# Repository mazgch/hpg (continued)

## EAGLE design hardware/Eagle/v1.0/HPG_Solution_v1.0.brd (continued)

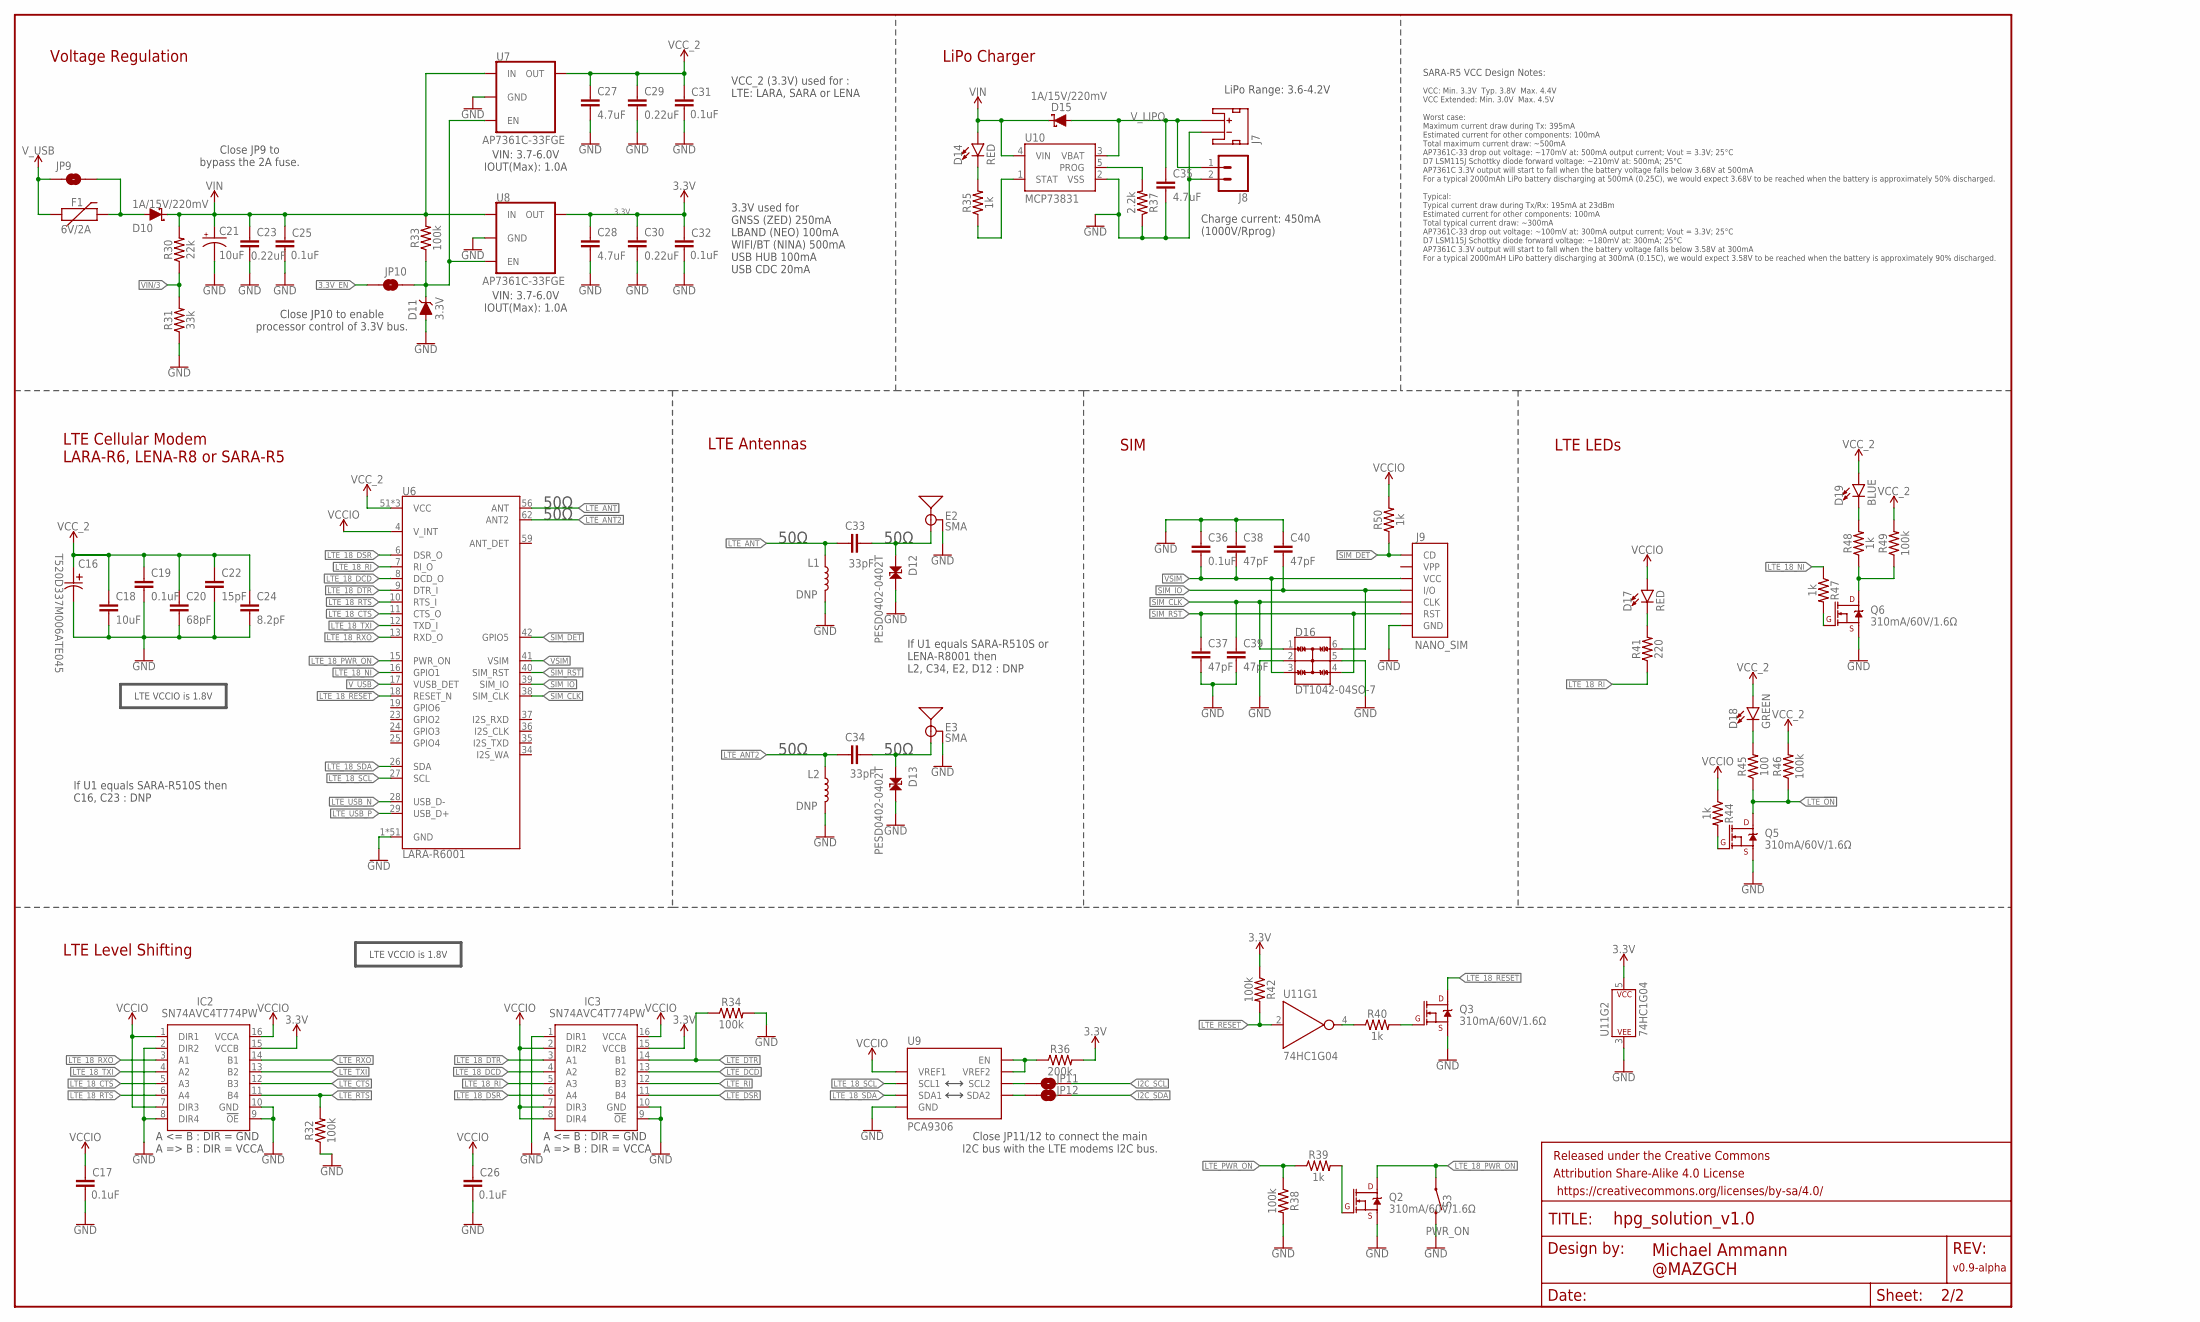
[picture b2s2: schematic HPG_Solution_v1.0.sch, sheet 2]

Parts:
C16: T520D337M006ATE045; CAPMP7.6X4.3_3.1N_KEM
C17, C19, C25, C26, C31, C32, C36: 0.1uF; 0603
C18: 10uF; 0603
C20: 68pF; 0603@1
C21: 10uF; EIA3216
C22: 15pF; 0603
C23, C29, C30: 0.22uF; 0603
C24: 8.2pF; 0603
C27, C28, C35: 4.7uF; 0603
C33, C34: 33pF; 0402
C37, C38, C39, C40: 47pF; 0603
D10, D15: 1A/15V/220mV; DO-214BA
D11: 3.3V; SOD-323
D12, D13: PESD0402-0402T; 0402-TIGHT
D14, D17: RED; LED-0603
D16: DT1042-04SO-7; SOT23-6L
D18: GREEN; LED-0603
D19: BLUE; LED-0603
E2, E3: SMA; SMA-EDGE
F1: 6V/2A; 1210
FRAME3: FRAME-LEDGER; CREATIVE_COMMONS
IC2, IC3: SN74AVC4T774PW; SOP65P640X120-16N
J7: JST_2MM_MALE; JST-2-SMD
J8: CONN_021X02_NO_SILK; 1X02_NO_SILK
J9: NANO_SIM; NANO_SIM_PP
JP9, JP10, JP11, JP12: JUMPER-SMT_2_NO_SILK; SMT-JUMPER_2_NO_SILK
L1, L2: DNP; 0402_COILCRAFT
Q2, Q3, Q5, Q6: 310mA/60V/1.6Ω; SOT323
R30: 22k; 0603
R31: 33k; 0603
R32, R33, R34, R38, R42, R46, R49: 100k; 0603
R35, R39, R40, R44, R47, R48, R50: 1k; 0603
R36: 200k; 0603
R37: 2.2k; 0603
R41: 220; 0603
R45: 100; 0603
S3: PWR_ON; TACTILE_SWITCH_SMD_5.2MM
U6: LARA-R6001; LARA-LGA
U7, U8: AP7361C-33FGE; UDFN-8
U9: PCA9306; VSSOP_8PIN
U10: MCP73831; SOT23-5
U11: 74HC1G04; SOT353

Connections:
3.3V: C28.1, C30.1, C32.1, IC2.15 (VCCB), IC3.15 (VCCB), R36.2, R42.1, U8.1 (OUT), U11.5 (P$V+); also elsewhere on the board
3.3V_EN: JP10.1; also elsewhere on the board
CHG_LED: R35.1, U10.1 (STAT)
GND: C16.2, C17.2, C18.2, C19.2, C20.2, C21.-, C22.2, C23.2, C24.2, C25.2, C26.2, C27.2, C28.2, C29.2, C30.2, C31.2, C32.2, C35.2, C36.1, C37.2, C38.1, C39.2, C40.1, D11.A, D12.2, D13.2, D16.2, D16.5, E2.GND@0 (GND), E2.GND@1 (GND), E2.GND@2 (GND), E2.GND@3 (GND), E3.GND@0 (GND), E3.GND@1 (GND), E3.GND@2 (GND), E3.GND@3 (GND), IC2.2 (DIR2), IC2.8 (DIR4), IC2.9 (!OE), IC2.10 (GND), IC3.1 (DIR1), IC3.9 (!OE), IC3.10 (GND), J7.1 (-), J8.2, J9.A1 (GND), J9.A2 (GND), J9.A3 (GND), J9.A4 (GND), J9.C5 (GND), L1.P$2 (2), L2.P$2 (2), Q2.2 (S), Q3.2 (S), Q5.2 (S), Q6.2 (S), R31.1, R32.1, R34.2, R37.1, R38.2, S3.3 (2), S3.4 (2), U6.1 (GND), U6.3 (GND), U6.5 (GND), U6.14 (GND), U6.20 (GND), U6.21 (GND), U6.22 (GND), U6.30 (GND), U6.32 (GND), U6.43 (GND), U6.50 (GND), U6.54 (GND), U6.55 (GND), U6.57 (GND), U6.58 (GND), U6.60 (GND), U6.61 (GND), U6.63 (GND), U6.64 (GND), U6.65 (GND), U6.66 (GND), U6.67 (GND), U6.68 (GND), U6.69 (GND), U6.70 (GND), U6.71 (GND), U6.72 (GND), U6.73 (GND), U6.74 (GND), U6.75 (GND), U6.76 (GND), U6.77 (GND), U6.78 (GND), U6.79 (GND), U6.80 (GND), U6.81 (GND), U6.82 (GND), U6.83 (GND), U6.84 (GND), U6.85 (GND), U6.86 (GND), U6.87 (GND), U6.88 (GND), U6.89 (GND), U6.90 (GND), U6.91 (GND), U6.92 (GND), U6.93 (GND), U6.94 (GND), U6.95 (GND), U6.96 (GND), U7.4 (GND), U7.EP (GND), U8.4 (GND), U8.EP (GND), U9.P1 (GND), U10.2 (VSS), U11.3 (P$V-); also elsewhere on the board
I2C_SCL: JP11.2; also elsewhere on the board
I2C_SDA: JP12.2; also elsewhere on the board
LTE_18_!RESET!: Q3.3 (D), U6.18 (RESET_N)
LTE_18_CTS: IC2.5 (A3), U6.11 (CTS_O)
LTE_18_DCD: IC3.4 (A2), U6.8 (DCD_O)
LTE_18_DSR: IC3.6 (A4), U6.6 (DSR_O)
LTE_18_DTR: IC3.3 (A1), U6.9 (DTR_I)
LTE_18_NI: R47.1, U6.16 (GPIO1)
LTE_18_PWR_ON: Q2.3 (D), S3.1, S3.2 (1), U6.15 (PWR_ON)
LTE_18_RI: IC3.5 (A3), R41.1, U6.7 (RI_O)
LTE_18_RTS: IC2.6 (A4), U6.10 (RTS_I)
LTE_18_RXO: IC2.3 (A1), U6.13 (RXD_O)
LTE_18_SCL: U6.27 (SCL), U9.P3 (SCL1)
LTE_18_SDA: U6.26 (SDA), U9.P4 (SDA1)
LTE_18_TXI: IC2.4 (A2), U6.12 (TXD_I)
LTE_!ON!: Q5.3 (D), R45.1, R46.1; also elsewhere on the board
LTE_!RESET!: R42.2, U11.2 (A); also elsewhere on the board
LTE_ANT: C33.1, L1.P$1 (1), U6.56 (ANT)
LTE_ANT2: C34.1, L2.P$1 (1), U6.62 (ANT2)
LTE_CTS: IC2.12 (B3); also elsewhere on the board
LTE_DCD: IC3.13 (B2); also elsewhere on the board
LTE_DSR: IC3.11 (B4); also elsewhere on the board
LTE_DTR: IC3.14 (B1), R34.1; also elsewhere on the board
LTE_PWR_ON: R38.1, R39.1; also elsewhere on the board
LTE_RI: IC3.12 (B3); also elsewhere on the board
LTE_RTS: IC2.11 (B4), R32.2; also elsewhere on the board
LTE_RXO: IC2.14 (B1); also elsewhere on the board
LTE_SCL: JP11.1, U9.P6 (SCL2)
LTE_SDA: JP12.1, U9.P5 (SDA2)
LTE_TXI: IC2.13 (B2); also elsewhere on the board
LTE_USB_N: U6.28 (USB_D-); also elsewhere on the board
LTE_USB_P: U6.29 (USB_D+); also elsewhere on the board
unnamed: C34.2, D13.1, E3.SIG (SIGNAL)
unnamed: D10.A, F1.2, JP9.2
unnamed: C33.2, D12.1, E2.SIG (SIGNAL)
unnamed: R37.2, U10.5 (PROG)
unnamed: D14.C, R35.2
unnamed: R36.1, U9.P7 (VREF2), U9.P8 (EN)
unnamed: Q2.1 (G), R39.2
unnamed: Q3.1 (G), R40.2
unnamed: R40.1, U11.4 (Y)
unnamed: D17.C, R41.2
unnamed: Q6.1 (G), R47.2
unnamed: Q6.3 (D), R48.1, R49.1
unnamed: D19.C, R48.2
unnamed: Q5.1 (G), R44.2
unnamed: D18.C, R45.2
unnamed: D11.C, JP10.2, R33.1, U7.5 (EN), U8.5 (EN)
SIM_CLK: C39.1, D16.1, J9.C3 (CLK), U6.38 (SIM_CLK)
SIM_DET: J9.CD, R50.1, U6.42 (GPIO5)
SIM_IO: C40.2, D16.6, J9.C7 (I/O), U6.39 (SIM_IO)
SIM_RST: C37.1, D16.4, J9.C2 (RST), U6.40 (SIM_RST)
VCCIO: C17.1, C26.1, D17.A, IC2.1 (DIR1), IC2.7 (DIR3), IC2.16 (VCCA), IC3.2 (DIR2), IC3.7 (DIR3), IC3.8 (DIR4), IC3.16 (VCCA), R44.1, R50.2, U6.4 (V_INT), U9.P2 (VREF1)
VCC_2: C16.1, C18.1, C19.1, C20.1, C22.1, C24.1, C27.1, C29.1, C31.1, D18.A, D19.A, R46.2, R49.2, U6.51 (VCC), U6.52 (VCC), U6.53 (VCC), U7.1 (OUT)
VIN: C21.+, C23.1, C25.1, D10.C, D14.A, D15.C, R30.2, R33.2, U7.8 (IN), U8.8 (IN), U10.4 (VIN); also elsewhere on the board
VIN/3: R30.1, R31.2; also elsewhere on the board
VSIM: C36.2, C38.2, D16.3, J9.C1 (VCC), U6.41 (VSIM)
V_LIPO: C35.1, D15.A, J7.2 (+), J8.1, U10.3 (VBAT)
V_USB: F1.1, JP9.1, U6.17 (VUSB_DET); also elsewhere on the board

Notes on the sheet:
SARA-R5 VCC Design Notes:
VCC: Min. 3.3V Typ. 3.8V Max. 4.4V VCC Extended: Min. 3.0V Max. 4.5V Worst case: Maximum current draw during Tx: 395mA Estimated current for other components: 100mA Total maximum current draw: ~500mA AP7361C-33 drop out voltage: ~170mV at: 500mA output current; Vout = 3.3V; 25°C D7 LSM115J Schottky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
Michael Ammann @MAZGCH
Voltage Regulation
VIN: 3.7-6.0V IOUT(Max): 1.0A
Close JP10 to enable processor control of 3.3V bus.
LiPo Charger
LiPo Range: 3.6-4.2V
Charge current: 450mA (1000V/Rprog)
VCC_2 (3.3V) used for : LTE: LARA, SARA or LENA
3.3V used for GNSS (ZED) 250mA LBAND (NEO) 100mA WIFI/BT (NINA) 500mA USB HUB 100mA USB CDC 20mA
Close JP9 to bypass the 2A fuse.
LTE Cellular Modem LARA-R6, LENA-R8 or SARA-R5
SIM
50Ω
LTE VCCIO is 1.8V
If U1 equals SARA-R510S then C16, C23 : DNP
LTE Antennas
If U1 equals SARA-R510S or LENA-R8001 then L2, C34, E2, D12 : DNP
LTE LEDs
LTE Level Shifting
Close JP11/12 to connect the main I2C bus with the LTE modems I2C bus.
v0.9-alpha

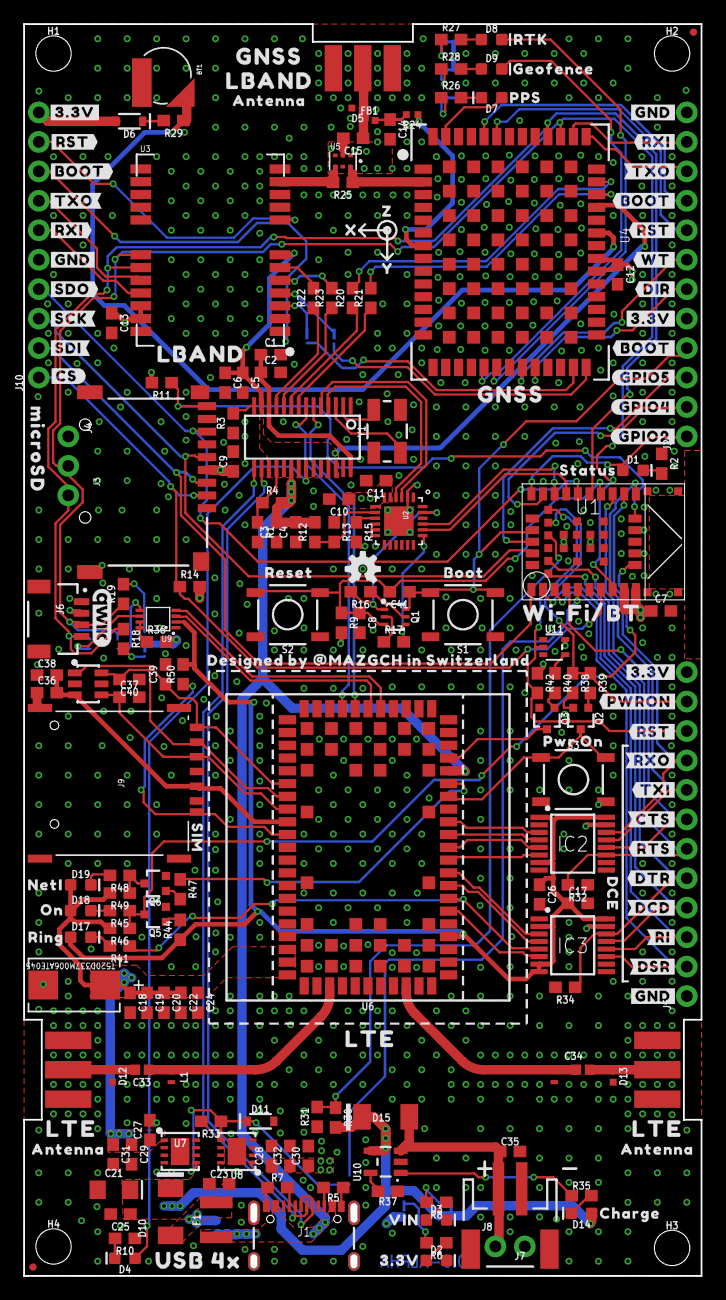
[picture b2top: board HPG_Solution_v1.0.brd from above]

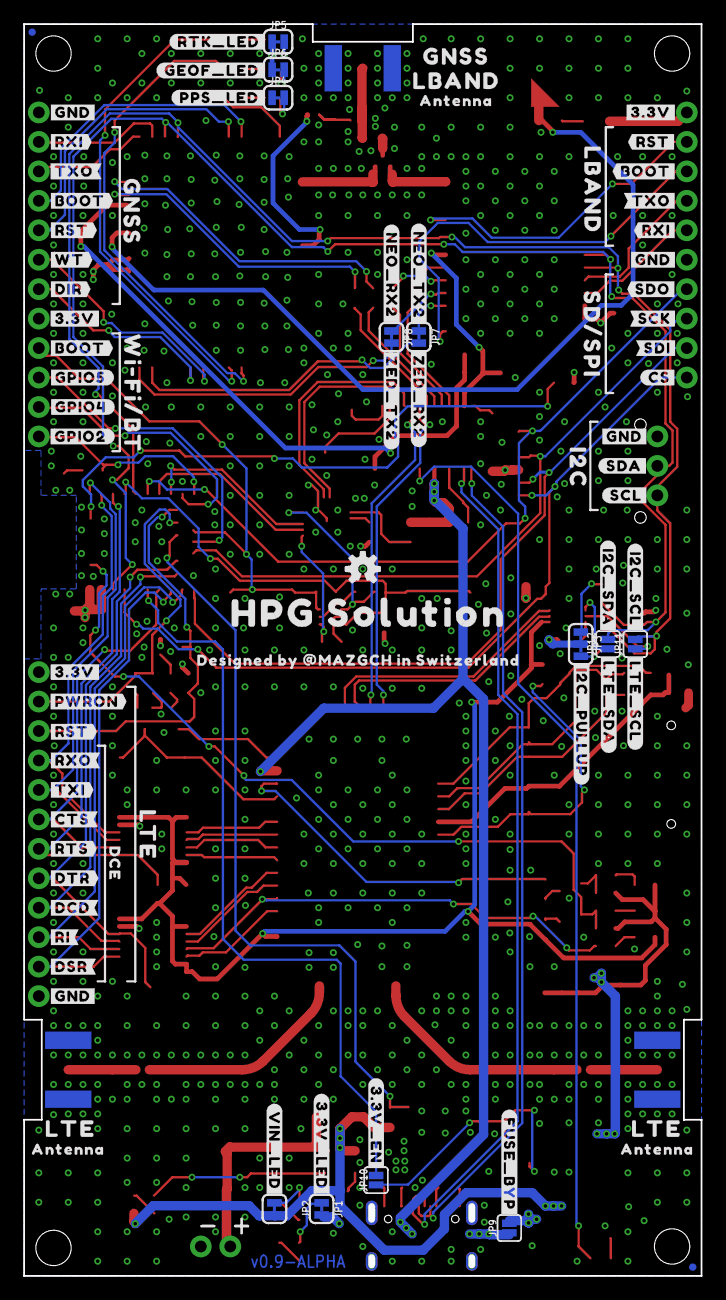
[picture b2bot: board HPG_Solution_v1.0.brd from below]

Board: 4 copper layers, 58.4 x 108.0 mm, 311 parts (84 on the bottom side), 141 nets.

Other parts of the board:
U$1, U$122: OSHW-LOGO-S
U$2: QWIIC_5MM
U$3: MICROSD0
U$4, U$5, U$19, U$44, U$45, U$118: LTE0
U$6, U$20, U$46, U$116: GNSS0
U$7: #PWRON#1
U$8, U$9, U$10, U$37, U$40, U$43, U$138: #GND#0
U$11, U$12, U$13, U$36, U$39, U$41: #3#3V#0
U$14, U$126, U$127: #RST#2
U$15: RESET6
U$16: BOOT5
U$17: PWR_ON0
U$18, U$22, U$35: #RST#3
U$21: CHARGE0
U$23: #RTK_LED#0
U$24: #3#3V_LED#0
U$25: 3#3V3
U$26: RTK16
U$27: #I2C_SCL#2
U$28: PPS14
U$29: #I2C_PULLUP#3
U$30, U$59: #RXI#1
U$31: ON0
U$32, U$33: #TXO#5
U$34: #CS#4
U$38, U$60: #RXI#0
U$42: #GEOF_LED#1
U$47: X1
U$48: Y2
U$49: #I2C_SDA#1
U$50: HPG_SOLUTION0
U$51: SIM0
U$52: Z0
U$53, U$75, U$76: #BOOT#1
U$54: VIN3
U$55: I2C0
U$56: #PWRON#0
U$57, U$72, U$74: #BOOT#0
U$58, U$61: #TXO#3
U$62: #PPS_LED#2
U$63: #GPIO4#1
U$64: #GPIO2#2
U$65: #GPIO2#8
U$66: #DIR#13
U$67: #WT#11
U$68: #WT#10
U$69: #DIR#12
U$70: #GPIO4#7
U$71: #GPIO5#6
U$73, U$114: DCE0
U$77, U$78, U$82, U$117: LBAND2
U$79: USB_4X3
U$80: RING0
U$81: STATUS7
U$83: #LTE_SCL#7
U$84, U$85, U$86, U$87, U$88, U$89: ANTENNA2
U$90, U$119: WI#FI#BT3
U$91: #3#3V_EN#1
U$92: #CTS#5
U$93: #DCD#4
U$94: #FUSE_BYP#2
U$95: #DSR#3
U$96: #DTR#7
U$97: #RI#6
U$98: #RXO#2
U$99: #RTS#8
U$100: #TXI#1
U$101: #RXO#3
U$102: #TXI#2
U$103: #CTS#6
U$104: #RTS#9
U$105: #DTR#8
U$106: #DCD#5
U$107: #RI#7
U$108: #DSR#4
U$109: #SCK#0
U$110: #NEO_RX2#0
U$111: #NEO_TX2#2
U$112: #ZED_RX2#3
U$113: #ZED_TX2#1
U$115: #GPIO5#0
U$120, U$121: DESIGNED_BY_#MAZGCH_IN_SWITZERLAND3
U$123: #LTE_SDA#5
U$124: #SCK#4
U$125: GEOFENCE5
U$128: #SDI#1
U$129: #VIN_LED#4
U$130: #SDO#2
U$131: #CS#3
U$132: #SDI#5
U$133: #SDO#6
U$134: SD#SPI8
U$135: NETI9
U$136: #SCL#11
U$137: #SDA#12

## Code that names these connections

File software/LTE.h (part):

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  /** constructor
   *  \note we do not pass the pins to the class as we prefer to be in control of them 
   */
  LTE() : SARA_R5{ PIN_INVALID/*LTE_PWR_ON*/, PIN_INVALID/*LTE_RESET*/, 3/*retries*/ } { 
    state = INIT;
    restart = false;
    ntripSocket = -1;
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      setState(CHECKSIM);  
    }
    while(true) {
      if ((PIN_INVALID != LTE_ON) && (state != INIT)) {
        // detect if LTE was turned off
        if (LTE_ON_ACTIVE != digitalRead(LTE_ON)) {
          UbxSerial.end();
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   *  The pins are defined in the HW.h file and depend on the board compiled for. 
   */
  void hwInit(void) {
    // The current SARA-R5 library is setting the LTE_RESET and LTE_PWR_ON pins to input after using them, 
    // This is not ideal for the v0.8/v0.9 hardware. Therefore it is prefered to control the LTE_RESET 
    // and LTE_PWR_ON externally in our code here. We also like to have better control of the pins to 
    // support different variants of LTE modems.
         
    // Module     Power On time   Power Off time   Reset
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    // LARA-R6    0.15-3.2s       >1.5s            0.05-6s (10s emergency)
    // LENA-R8    >2s             >3.1s            0.05s
    
    // The LTE_RESET pin is active LOW, HIGH = idle, LOW = in reset
    // The LTE_RESET pin unfortunately does not have a pull up resistor on the v0.8/v0.9 hardware
    if (PIN_INVALID != LTE_RESET) {
      HW::pinModeWrite(LTE_RESET, HIGH);
    }
    // The LTE_PWR_ON pin is usually active HIGH, LOW = idle, defined by LTE_PWR_ON_ACTIVE, active timings see table above
    // The LTE_PWR_ON pin has a external pull low resistor on the board. 
    if (PIN_INVALID != LTE_PWR_ON) {
      HW::pinModeWrite(LTE_PWR_ON, !LTE_PWR_ON_ACTIVE);
    }
    if (PIN_INVALID != LTE_TXI) {
      HW::pinModeWrite(LTE_TXI, HIGH);
    }
    if (PIN_INVALID != LTE_RTS) {
      HW::pinModeWrite(LTE_RTS, LOW);
    }
    if (PIN_INVALID != LTE_DTR) {
      HW::pinModeWrite(LTE_DTR, LOW);
    } 
    // init all other pins here
    if (PIN_INVALID != LTE_ON)  pinMode(LTE_ON,  INPUT);
    if (PIN_INVALID != LTE_RXO) pinMode(LTE_RXO, INPUT);
    if (PIN_INVALID != LTE_CTS) pinMode(LTE_CTS, INPUT);
    if (PIN_INVALID != LTE_DSR) pinMode(LTE_DSR, INPUT);
    if (PIN_INVALID != LTE_DCD) pinMode(LTE_DCD, INPUT); 
    if (PIN_INVALID != LTE_RI)  pinMode(LTE_RI,  INPUT);
    if (PIN_INVALID != LTE_INT) pinMode(LTE_INT, INPUT);
  }

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    // turn on the module 
    #define DETECT_DELAY 100
    int pwrOnTime = -1; // will never trigger
    if (PIN_INVALID != LTE_PWR_ON) {
      if ((PIN_INVALID != LTE_ON) ? LTE_ON_ACTIVE != digitalRead(LTE_ON) : true) {
        log_i("LTE power on");
        digitalWrite(LTE_PWR_ON, LTE_PWR_ON_ACTIVE);
        pwrOnTime = LTE_POWER_ON_PULSE / DETECT_DELAY;
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        pwrOnTime = -1; // no more
        i = 0; // restart timer
      }
      if (PIN_INVALID != LTE_RXO) {
        char rxo = digitalRead(LTE_RXO);
        if (lastRxo != rxo) {
          log_d("LTE pin RXO %s", (rxo == LOW) ? "LOW(active)" : "HIGH(idle)"); 
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        }
        ready = ready && (rxo == HIGH);
      }
      if (PIN_INVALID != LTE_ON) {
        char on = digitalRead(LTE_ON);
        if (on != lastOn) {
          log_d("LTE pin ON %s", (on == LTE_ON_ACTIVE) ? "on(active)" : "off(idle)"); 
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        }
        ready = ready && (on == LTE_ON_ACTIVE);
      }
      if (PIN_INVALID != LTE_CTS) {
        char cts = digitalRead(LTE_CTS);
        if (lastCts != cts) {
          log_d("LTE pin CTS %s", (cts == LOW) ? "LOW(idle)" : "HIGH(wait)"); 
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    if (ready) {
      #define PIN_TXT(pin) (PIN_INVALID == pin) ? "" : digitalRead(pin) == LOW ? " LOW" : " HIGH"
      log_d("baudrate %d pins RXo %d%s TXi %d%s CTSo %d%s RTSi %d%s", LTE_BAUDRATE, 
        LTE_RXO, PIN_TXT(LTE_RXO), LTE_TXI, PIN_TXT(LTE_TXI),
        LTE_CTS, PIN_TXT(LTE_CTS), LTE_RTS, PIN_TXT(LTE_RTS));
      ready = begin(UbxSerial, LTE_BAUDRATE);
    }
    return ready;
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    delay(100);
    UbxSerial.end();
    delay(10);
    log_d("LTE baudrate %d pins RXo %d TXi %d CTSo %d RTSi %d", baud, LTE_RXO, LTE_TXI, LTE_CTS, LTE_RTS);
    UbxSerial.begin(baud, SERIAL_8N1, LTE_RXO, LTE_TXI);
    if ((PIN_INVALID != LTE_RTS) && (PIN_INVALID != LTE_CTS)) {
      UbxSerial.setPins(LTE_RXO, LTE_TXI, LTE_CTS, LTE_RTS); 
      UbxSerial.setHwFlowCtrlMode(HW_FLOWCTRL_CTS_RTS, 64);
    }
    delay(100);
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
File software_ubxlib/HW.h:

/*
 * Copyright 2022 by Michael Ammann (@mazgch)
 *
 * Licensed under the Apache License, Version 2.0 (the "License");
 * you may not use this file except in compliance with the License.
 * You may obtain a copy of the License at
 *
    http://www.apache.org/licenses/LICENSE-2.0
 *
 * Unless required by applicable law or agreed to in writing, software
 * distributed under the License is distributed on an "AS IS" BASIS,
 * WITHOUT WARRANTIES OR CONDITIONS OF ANY KIND, either express or implied.
 * See the License for the specific language governing permissions and
 * limitations under the License.
 */
 
#ifndef __HW_H__
#define __HW_H__

#if defined(ARDUINO_UBLOX_NINA_W10)
 #define HW_TARGET     MAZGCH_HPG_SOLUTION_V09
#elif defined(ARDUINO_UBLOX_NORA_W10)
 #define HW_TARGET     MAZGCH_HPG_MODULAR_V01
#elif defined(ARDUINO_ESP32_MICROMOD)
 #define HW_TARGET     SPARKFUN_MICROMOD_MAINBOARD
#else
 #error unknown board target 
#endif

#define MAZGCH_HPG_SOLUTION_V08              0 // Select ESP32 Arduino / u-blox NINA-W10 series (ESP32) 
#define MAZGCH_HPG_SOLUTION_V09              1 // Select ESP32 Arduino / u-blox NINA-W10 series (ESP32) 
#define MAZGCH_HPG_SOLUTION_V10              2 // Select ESP32 Arduino / u-blox NINA-W10 series (ESP32) 

#define MAZGCH_HPG_MODULAR_V01               5 // Select ESP32 Arduino / u-blox NORA-W10 series (ESP32-S3), LTE in slot 1

#define SPARKFUN_MICROMOD_MAINBOARD_PT      11 // Choose Spakfun ESP32 Arduino / Sparkfun ESP32 MicroMod / prototype LTE function
#define SPARKFUN_MICROMOD_MAINBOARD         12

#define SPARKFUN_MICROMOD_MAINBOARD_DOUBLE  21 // Choose Spakfun ESP32 Arduino / Sparkfun ESP32 MicroMod 

#define SPARKFUN_MICROMOD_ASSET_TRACKER     10 // Choose Spakfun ESP32 Arduino / Sparkfun ESP32 MicroMod

enum HW_PINS {  
    // Standard pins
    BOOT         = 0, 
#if (HW_TARGET == MAZGCH_HPG_MODULAR_V01)
    LED         =  8,
    CDC_RX      = 44,  CDC_TX         = 43,
    CAN_RX      = -1,  CAN_TX         = -1,
    I2C_SDA     = 18,  I2C_SCL        = 17,
#else
    LED         =  2,
    CDC_RX      =  3,  CDC_TX         = 1,
    CAN_RX      =  4,  CAN_TX         = 5,
    I2C_SDA     = 21,  I2C_SCL        = 22,
#endif    
#if (HW_TARGET == MAZGCH_HPG_SOLUTION_V08)
    // LTE (DCE) - BUG 34/39 are input only.on V0.8 -> will swap in V0.9
    LTE_RESET   = -1 /*BUG 34 is IN only */, 
    LTE_PWR_ON  = -1 /*BUG 39 is IN only */,  LTE_ON        = 37,  LTE_INT = -1,
    LTE_TXI     = 25,   LTE_RXO        = 26,  LTE_RTS       = 27,  LTE_CTS = 36, 
    LTE_RI      = 12,   LTE_DSR        = 13,  LTE_DCD       = 14,  LTE_DTR = 15,

    // Power supply
    VIN         = 35,   V33_EN         = 33,
    
    // Micro SD card - MISO / MOSI will be swapped to allow use of default pins 
    MICROSD_SCK  = 18,  MICROSD_SDI    = 23,  MICROSD_SDO   = 19,
    MICROSD_CS   = 32,  MICROSD_PWR_EN = -1,  MICROSD_DET   = 38,
    
#elif (HW_TARGET == MAZGCH_HPG_SOLUTION_V09)
    // LTE (DCE)
    LTE_RESET    = 13,  LTE_PWR_ON     = 12,  LTE_ON        = 37,  LTE_INT = -1,
    LTE_TXI      = 25,  LTE_RXO        = 26,  LTE_RTS       = 27,  LTE_CTS = 36, 
    LTE_RI       = 34,  LTE_DSR        = 39,  LTE_DCD       = 14,  LTE_DTR = 15,

    // Power supply
    VIN          = 35,  V33_EN         = 33,
    
    // Micro SD card
    MICROSD_SCK = SCK,  MICROSD_SDI  = MISO,  MICROSD_SDO = MOSI,
    MICROSD_CS   = 32,  MICROSD_PWR_EN = -1,  MICROSD_DET   = 38,
    
#elif (HW_TARGET == MAZGCH_HPG_SOLUTION_V10)
    // LTE (DCE)
    LTE_RESET    = 12,  LTE_PWR_ON     = 13,  LTE_ON        = 37,  LTE_INT = -1,
    LTE_TXI      = 25,  LTE_RXO        = 26,  LTE_RTS       = 27,  LTE_CTS = 36, 
    LTE_RI       = 34,  LTE_DSR        = 39,  LTE_DCD       = 14,  LTE_DTR = 15,

    // Power supply
    VIN          = 35,  V33_EN         = 33,
    
    // Micro SD card
    MICROSD_SCK = SCK,  MICROSD_SDI  = MISO,  MICROSD_SDO = MOSI, // = default SCK / MISO / MOSI    
    MICROSD_CS   = 32,  MICROSD_PWR_EN = -1,  MICROSD_DET   = 38,
    
#elif (HW_TARGET == MAZGCH_HPG_MODULAR_V01)
    // LTE (DCE)
    LTE_RESET    = -1,  LTE_PWR_ON     =  9,  LTE_ON        = -1,  LTE_INT = -1,
    LTE_TXI      = 46,  LTE_RXO        =  2,  LTE_RTS       = 38,  LTE_CTS =  4, 
    LTE_RI        = 7,  LTE_DSR        = -1,  LTE_DCD       = -1,  LTE_DTR = -1,

    // Power supply
    VIN          = -1,  V33_EN         = -1,
    
    // Micro SD card
    MICROSD_SCK = SCK,  MICROSD_SDI  = MISO,  MICROSD_SDO = MOSI,
    MICROSD_CS   = 34,  MICROSD_PWR_EN = -1,  MICROSD_DET   = -1,
    
#elif (HW_TARGET == SPARKFUN_MICROMOD_ASSET_TRACKER)
    // LTE (DCE)
    LTE_RESET    = -1,  LTE_PWR_ON     = G2,  LTE_ON        = G6,  LTE_INT = G5, 
    LTE_TXI     = TX1,  LTE_RXO       = RX1,  LTE_RTS       = -1,  LTE_CTS = -1, 
    LTE_RI       = G4,  LTE_DSR        = -1,  LTE_DCD       = -1,  LTE_DTR = -1,
   
    // Power supply
    VIN          = 39,  V33_EN         = -1,
    
    // Micro SD card
    MICROSD_SCK = SCK,  MICROSD_SDI  = MISO,  MICROSD_SDO = MOSI, // = default SCK / MISO / MOSI
    MICROSD_DET  = -1,  MICROSD_PWR_EN = G1,  
    MICROSD_CS   = G0,

#elif ((HW_TARGET == SPARKFUN_MICROMOD_MAINBOARD_PT) || (HW_TARGET == SPARKFUN_MICROMOD_MAINBOARD_DOUBLE_PT)) // using ESP 32 MicroMod MCU
    // LTE (DCE)   // assignable D0,A0,G0 (G4 G5 can't be used as duplicated on ESP32)
    LTE_RESET    = G2,  LTE_PWR_ON   = PWM0,  LTE_ON        = -1/*BUG G3/TX1*/,  LTE_INT = -1, 
    LTE_TXI     = TX1,  LTE_RXO       = RX1,  LTE_RTS       = -1,  LTE_CTS = -1,  // TX1/RX1 were swapped, all PT V1 boards patched
    LTE_RI       = G1,  LTE_DSR        = -1,  LTE_DCD       = -1,  LTE_DTR = -1,
    LTE_NI       = -1, /*BUG G4/RXD*/
    // Power supply
    VIN          = 39,  V33_EN         = -1,
    
    // Micro SD card
    MICROSD_SCK = SCK,  MICROSD_SDI  = MISO,  MICROSD_SDO = MOSI,
    MICROSD_DET  = -1,  MICROSD_PWR_EN  = 5,  
# if (HW_TARGET == SPARKFUN_MICROMOD_MAINBOARD_PT)
    MICROSD_CS   = D1,
# else
    MICROSD_CS   = G4,
# endif

#else // using ESP 32 MicroMod MCU
    // LTE (DCE)   // assignable D0,A0,G0 (G3/G4 can't be used as duplicated with TX1/RX1 on ESP32)
    LTE_RESET  = PWM0,  LTE_PWR_ON     = G2,  LTE_ON        = SS,  LTE_INT = -1, 
    LTE_TXI     = TX1,  LTE_RXO       = RX1,  LTE_RTS       = -1,  LTE_CTS = -1, 
    LTE_RI       = -1,  LTE_DSR        = -1,  LTE_DCD       = -1,  LTE_DTR = -1,
    LTE_NI       = D0,
    // Power supply
    VIN          = 39,  V33_EN         = -1,
    
    // Micro SD card
    MICROSD_SCK = SCK,  MICROSD_SDI  = MISO,  MICROSD_SDO = MOSI, 
    MICROSD_DET  = -1,  MICROSD_PWR_EN  = 5,  
# if (HW_TARGET == SPARKFUN_MICROMOD_MAINBOARD)
    MICROSD_CS   = D1,
# else
    MICROSD_CS  = G4,
# endif

#endif
    PIN_INVALID = -1
};

#define HW_DBG_PIN(pin,level) if (PIN_INVALID != pin) pinMode(pin, OUTPUT), digitalWrite(pin,level)
#define HW_DBG_HI(pin)        HW_DBG_PIN(pin,HIGH)
#define HW_DBG_LO(pin)        HW_DBG_PIN(pin,LOW)

#define HW_DBG_WLAN           PIN_INVALID//D1
#define HW_DBG_LTE            PIN_INVALID//D0
#define HW_DBG_GNSS           PIN_INVALID//PWM1
#define HW_DBG_LBAND          PIN_INVALID//PWM1
#define HW_DBG_WLAN_MGR       PIN_INVALID//PWM0
#define HW_DBG_LOG_ERR        PIN_INVALID

#endif // __HW_H__

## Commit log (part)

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2022-09-28 Rename Vehicles.md to Vehicle.md
2022-09-29 Allow to set a JSON instead of Device Profile Token
2022-09-30 minor teaks in usability
2022-10-02 finalized the mower ticks conversions and integration to enable fusion mode.
2022-10-02 change to default TX1 pin
    - loose status led (shows now TX1)
2022-10-02 Picture of the final prototype.
2022-10-02 apply speed calibration
2022-10-02 fix documentation and cleanup
2022-10-04 minor change
2022-10-07 test code: repeat write attempts on sd card
2022-10-07 rework the ESF-MEAS injection from CAN bus
    - not using I2C now using Serial2 to ZED-RXI this avoids long unpredictable latencies caused by larger i2C message injection or reads
    - need to wire up a spare GPIO (e.g LTE_DTR or V33_EN) to ZED-RXI
    - Can bus needs to be enabled by uncommenting its header in software.ino and setting the AUTOMOTIVE dynamic model
2022-11-11 some workarounds for LENA-R8
    This commit relies on changes in the SARA-R5 driver when used with LENA-R8
2022-11-24 Fix HTTPs on LENA-R8001
    - Seems that HTTPS port is not automatically set to 443 when security is enabled.
2022-11-26 better parsing of LBAND / QZSS data
2022-11-26 better flicker free display of LBAND signals
2022-11-28 basic ntrip client over WiFi
2022-11-30 small fix
2022-11-30 another fix
2022-12-07 must select PP source to none to use NTRIP
2022-12-09 NTRIP: dynamically alloc the buffer for RTCM data and sed as one.
2022-12-09 code that allows to pass the written messages to the GUI
2022-12-09 enable the LBAND C/N0 reporting
2022-12-09 improve signal display
2022-12-09 fix transition between LTE and NTRIP LTE config
2022-12-12 cleanup & simplify
    - bind
    - location of LUT tables
    log in LBAND
2022-12-12 fix Websocket
    - fixed websocket
    - cleanup bluetooth (reguires bigger flash/partition)
    - TODO/BUG BT connection immediately lost
2022-12-12 BLUETOOTH functional
    - Bluetooth LE based Nordic Uart service
    - allows to connect with SW Maps for visualisation and ntrip data
    - fixed debug mode compile and degraded and fixed several messages to verbose
    - provide heap diagnostics.
2022-12-13 Part 1 of docu
    - docu drop: software, BT, CANBUS, GNSS, LBAND LTE, LOG, UBXFILE
    - allow to set own log level.
    - timeouts reworked
2022-12-14 Part 3: doc update
    - major docu for WEBSOCKET, WLAND, CONFIG
    - dump the source table (on wifi)
    - fix the bluetooth u-blox serial port
2022-12-14 Part 4: fixes
    - clean BLE uart code (SPS still flacky)
    - combine server:port/mountpoint NTRIP config
    - fixes in html/js
2022-12-14 remove CAN by default.
2022-12-14 late fixes
    - switch BLE to NORDIC
    - stack adjustments
    - fix lena ignore command
2022-12-15 final changes after code rework / docu
    - disable BT by default
    - fix stack sizes
    - extra warning about low memory during WIFI ssl init, triggered by MQTT connection rsulting failure in error refused
2022-12-15 tested with new release of wifimanager
    - seems faster
2022-12-15 argh ...
2022-12-15 major refactoring of code and documentation (and some features) (#11)
    - CODE: reorganised the code by split large functions up by topic to make it better readable and understandable
    - DOCU: briefly documented all functions and their arguments
    - BLUETOOTH now support both NUS and u-blox SPS
    - WEBSOCKET: now outputs also data from LBAND, LTE and WLAN services
    - CONSOLE: You can set the debug level of the application independently from Arduinos debug level.
    - CONSOLE: report heap usage an stack usage of the tasks
2022-12-17 avoid errors on mobile, if link is redirected to an app
2022-12-17 manage LBAND + CLAS receiver mode
    - this prevents LBAND message to be injected while de-configured or outside supported coverage
    - you may still see the MON-PMP
2022-12-22 new CONFIG and IPC
    - CONFIG: using Preferences
    - IPC: standardise communication between tasks
2022-12-24 using IPC queues, pipes and messages
    - this greatly improves the memory and stack usage
    - sd card task needs to be improved, use better FS
2022-12-26 - adjusted stacks / comments
    - lots of comments
    - adjusted the stacks
    - change the keys config get/set
2022-12-28 SPARTN decoding
    - fixed hexdump special chars ><&
    - only feed UBX and NMEA to the epoch
2022-12-28 some progress switching BT
2022-12-29 seems more stable with selective BLUETOOTH
    - BLUETOOTH is disabled when PointPerfect is enabled on WLAN.
2022-12-30 rework IPC to use hint instead of content
    - IPC now uses hints
    - properly switch off LBAND (offer alternative code)
    - rework use source with hints
    - implement CANBUS using commQueue (front insert)
2023-01-02 just some trial parsing code
2023-01-02 Update engine.js (#13)
2023-01-02 two fixes
2023-01-05 try fix favicon
2023-01-05 move after title
2023-01-21 stable version
    - TODO debug small minAllocSize
2023-02-11 added adapter board for open mower
2023-02-11 extract RXM-COR / more flexible ips
    - allow to connect to ips with port and /ws
    - extract rxm cor ebn0
2023-02-11 add ota button
2023-02-11 make it compile with new HW.h
2023-02-11 allow - as source
2023-02-11 added uptime and fix caps of labels
2023-02-12 fix LTE MQTT FSM
2023-02-12 draw protection level ellipse
2023-02-19 better styling and color management
2023-02-19 switch to rgb
2023-02-19 migration to newer libraries
    - add full screen mode
    - rearrange some map buttons
    - todo: chart.js 4.2.1, ver 4.x does not yet work somehow
2023-02-19 try fix ios
2023-02-19 fix append of port
2023-02-20 keep the tools buttons same size
2023-02-21 add hAcc circle, fix js error
2023-02-22 attempt to make XPLR-HPG work
2023-02-22 few more html issues
2023-02-22 disable spell check
2023-03-23 fix rotating logo in zoomed mode. Avoid error with bad IPs.
2023-05-01 changed MGA defines
2023-05-23 Prepare for official u-blox release XPLR-HPG1/2
    - renamed official u-blox targets
    - minor tweaks
    - update readme and reference to official boards.
2023-06-29 update versions to latest
    - added overlay icon
    - fixed monitor string parsing when no source
    - as used for customer N investigations
2023-07-13 Update README.md (#15)
    clarified back and green edition
2023-11-03 Add SD PWR_EN inversion. Add HW hwInit
2023-11-06 Remove INVERTED. Add REQUIRED_GPIO_PIN
2023-11-06 Add support for the SparkFun RTK Everywhere (#16)
    * Add SPARKFUN_RTK_EVERYWHERE
    * Add special GPIO handling SD PWR_EN inversion. Add HW hwInit, REQUIRED_GPIO_PIN
    thanks @PaulZC
2024-02-07 Fix bug in mqttCallback UNSUBSCRIBE (#17)
2024-04-20 Test with latest version, add support for secure NTRIP, VIN monitor
    - Adding VIN voltage reading at start
    - Support Secure NTRIP connections on WIFI such as on PointPerfect 2102 port.
    - Draft Secure NTRIP connections on WIFI such as on PointPerfect 2102 port, requires new API in sparkfun SARA-R5 lib
    - tested with latest libraries, somehow however ESP32 2.0.10 and later crashes immediately after boot with a CRC error
2024-04-20 Adding template code to enable secure PP over NTRIP
    currently disabled and requires latest changes to sparkfun library.
2024-04-21 backup override to have a option to set TLS on socket
    to be removed when PR https://github.com/sparkfun/SparkFun_u-blox_SARA-R5_Arduino_Library/pull/43/ is merged and released
2024-04-21 Auto detect secure and non secure sockets for NTRIP
    - also wipe pointer after deleting
2024-04-21 get ports on page load
2024-04-22 possibility to set http or https protocol
    this adds better paring of ntrip server url
2024-04-27 NTRIP improvements
    - make NTRIP client work with pointperfect/onocoy/rtk2go
    - reconnect also LTE after config changes
    - support secure and non secure NTRIP connections
    - using HTTP client for NTRIP over WIFI
    - compile time switches for NTRIP 1.0/2.0, and HTTP 1.0 / 1.1
2024-04-28 improved config page
    - rework the config page to save memory
    - add ntrip version selection
2024-04-29 improve https: alert and redirect
2024-04-29 use open
2024-04-30 decoding flags
2024-05-01 make the green PCB version default,
2024-05-02 name the board, better debug output
2024-05-11 add Navic Msg and Fix Date Day of Month
2024-05-29 fixing a debug message typo
2024-05-29 Update LTE.h
    adding some debug messages
2024-05-29 Update LTE.h (#24)
    adding some debug messages
2024-05-29 prepare for esp32_arduinov3.0.0
    - BOOT pin pull up must be set
    - Ringbuffer can't be size 0
    - you may need to patch ArduinoWebsockets https://github.com/gilmaimon/ArduinoWebsockets/issues/156
    - avoid some -wFormat= warnings (better disable completely as wifimanager, SARA-R5 and other libs are affected)
2024-06-03 better comments for working around issues with v3.0.0
2025-01-02 port to new library and compiler versions
    - remove various warnings
    - avoid use of deprecated functions
    - improve sara r5 error message in case of socket failure
2025-07-23 [Autofic] Create package.json and CI workflow
2025-07-23 chore: remove CI workflow before upstream PR
2025-07-24 [Autofic] 2 malicious code detected!!
2025-07-27 added viewer
2025-07-27 parse version and new style
2025-07-28 move parts needed to a new module
2025-07-28 fix small add remove layer issue
2025-08-10 viewer changes
    - ui improvements
    - charts
    - reference offsets
    - better config files
    - handle gz files.
2025-08-10 improve the css
2025-08-10 add stats in chart
    reference lines for cfg and shown when hovering a series
2025-08-10 add copyright
2025-08-15 got more stuff working
    cfg, histo, click on chart, time slider
2025-08-15 restore time range
2025-08-15 styling fix
2025-08-15 fixing issues on chome
    - adding cumulative / derivative option
2025-08-15 fixing the tips
2025-08-21 adding own trimPlayer
    tuning of user interface
2025-08-22 fixing places and datetime parsing
2025-08-24 - several imprvements.
    - added google maps,
    - fix native zoom levels
    - speed up gzip/ungzip and text decodning
    - crosshair not interactive
2025-08-24 remove google maps trial
2025-08-24 migrating to modules
    added PSM plots
2025-08-24 fix NAV-STATUS fixType
2025-08-24 ignore some working folders
2025-08-24 improve dots and colors in tables
2025-08-25 adding back hammer for gesture support in chart
2025-08-29 before chart view migration
    - map view working also speedup
2025-08-29 added crop feature
2025-08-31 major ui reworking
    new fileManager
    added tableView
2025-08-31 add fft, select param by table
    - filter tracks in table
    - improve hover in map.
    - select chart field by table
2025-09-01 fix last minor Ui issues
2025-09-01 fix pt colors
2025-09-01 fft dB, ui fixes.
    - fft in dB / lin
    - fixing UI issues chip update
    - fixing reference error issues.
    - placement of the chip popup
    - player map repositioning
2025-09-02 most of the cleanup done
2025-09-02 crossHair fix
2025-09-02 one more crossHair fix.
2025-09-02 don't set alpha
2025-09-03 fix ref errors
2025-09-03 better color handling, add remove ui
2025-09-03 fix crossHair Marker
2025-09-05 Update placesManager.js (#34)
2025-09-05 Update viewer.js (#35)
2025-09-05 Update placesManager.js (#36)
2025-09-06 improve UI with chart buttons
2025-09-22 bump some lib versions
2025-09-22 improve the track handling
2025-09-24 ProtocolUnknowm problem reported by Pawel
2025-09-29 fix refErrorCalc
2025-10-29 Update field.js
    fix integer cleaning (e.g. odometer, svs)
2025-11-03 show 0 values in table
2025-11-03 more sv plots
    - satellite positions
    - satellite residuals
    - using d3 for ploting
2025-11-03 no 0 residuals
2025-11-03 better colors and
2025-12-30 adding experimental ble support
    supports NUS service
2026-01-03 improve sv parsing (M8)
    todo GRS may still by buggy if multiple GNGSA are sent
2026-01-08 calc more errors
2026-01-08 fix the cog error
2026-01-10 limit track names
2026-01-11 severa gui improvements
    - move gui element inside views
    - make pills smaller
    - template colors (disabled)
    - draft for landscape mode (disabled)
2026-01-11 sort svs in signalbar table
2026-01-12 Improve parsing for Mosaci X5
    allow multiple GNS messages with different takers e.g.:
    $GNGNS,074631.00,2232.54530024,N,11401.37477057,E,AAAA,41,0.4,7.95017,-2.19649,,,V*32
    $GPGNS,074631.00,,,,,,09,,,,,,V*17
    $GLGNS,074631.00,,,,,,07,,,,,,V*05
    $GAGNS,074631.00,,,,,,06,,,,,,V*09
    $GBGNS,074631.00,,,,,,19,,,,,,V*04
2026-01-12 Handle undefined values in sortKey function
2026-01-12 old signal chart removed
2026-01-12 add tiles to all sections, move help
2026-01-14 Show signal on separate line in tooltip
2026-01-15 fix GNS message
    Removed commented-out fields from NMEA protocol definitions.
2026-01-15 improve sv decoding
2026-01-18 draft a supply message
    extract VCC power
2026-01-18 fix viewer and at parser
2026-02-20 fix ble, not timeout with ble/usb
2026-02-23 Update regex to include additional NMEA message types
2026-03-02 add nav sig
2026-03-02 min width
2026-03-15 cleanup
2026-03-21 do not fail during cleanup, fix evkmeas
2026-05-13 extract more info for a file
2026-05-15 check before
